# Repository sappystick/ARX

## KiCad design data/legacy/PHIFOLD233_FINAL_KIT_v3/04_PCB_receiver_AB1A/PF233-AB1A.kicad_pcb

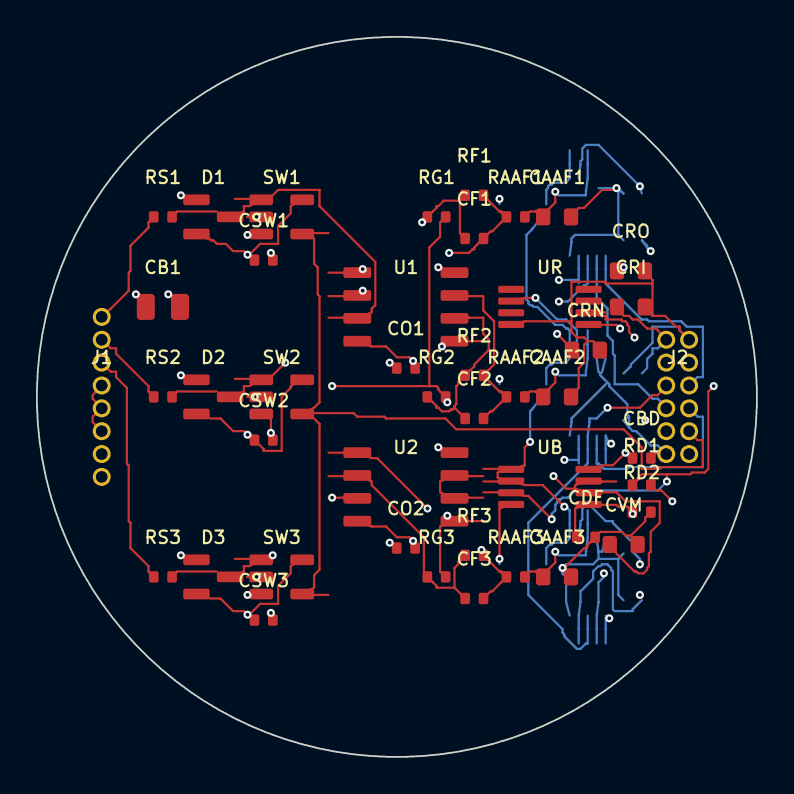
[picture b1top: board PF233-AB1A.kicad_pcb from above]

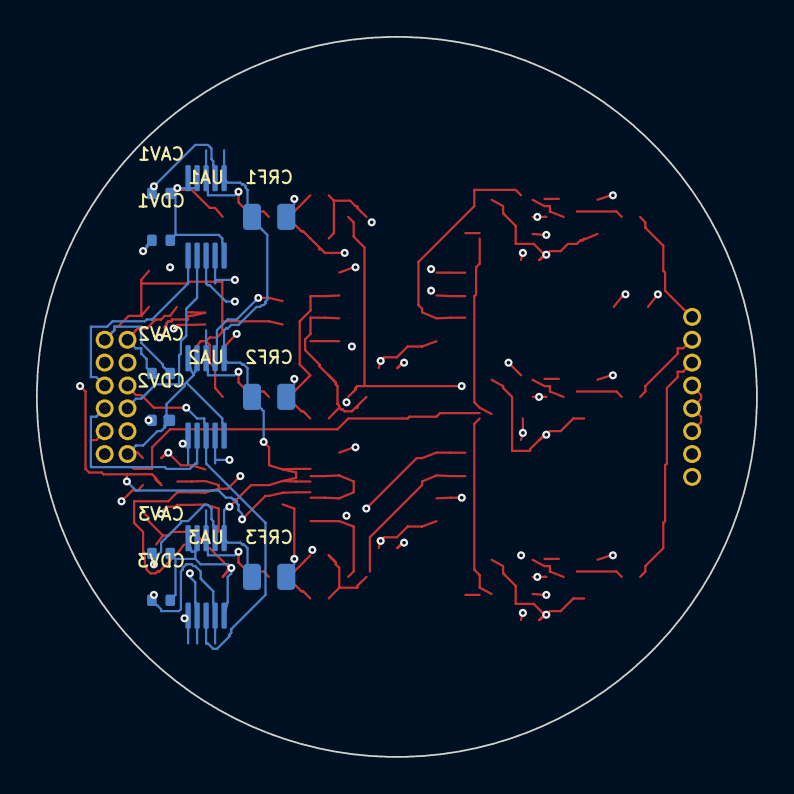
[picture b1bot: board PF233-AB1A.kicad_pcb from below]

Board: 6 copper layers, 40.0 x 40.0 mm, 56 parts (12 on the bottom side), 30 nets.

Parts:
CAAF1, CAAF2, CAAF3: 2n2; C_0603_1608Metric
CAV1, CAV2, CAV3: 100n; C_0402_1005Metric
CB1: 10u; C_0805_2012Metric
CBD: 100n; C_0402_1005Metric
CDF: 100n; C_0402_1005Metric
CDV1, CDV2, CDV3: 100n; C_0402_1005Metric
CF1, CF2, CF3: 22p; C_0402_1005Metric
CO1, CO2: 100n; C_0402_1005Metric
CRF1, CRF2, CRF3: 10u; C_0805_2012Metric
CRI: 1u; C_0603_1608Metric
CRN: 1u; C_0603_1608Metric
CRO: 1u; C_0603_1608Metric
CSW1, CSW2, CSW3: 100n; C_0402_1005Metric
CVM: 1u; C_0603_1608Metric
D1, D2, D3: BAV199; SOT-23
J1: Antenna harness 8p solder pads 1.27mm; PinHeader_1x8_P1.27mm
J2: Main-board 2x6 1.27mm header; PinHeader_2x6_P1.27mm
RAAF1, RAAF2, RAAF3: 200; R_0402_1005Metric
RD1, RD2: 10k; R_0402_1005Metric
RF1, RF2, RF3: 390; R_0402_1005Metric
RG1, RG2, RG3: 10; R_0402_1005Metric
RS1, RS2: 100; R_0402_1005Metric
RS3: 1000; R_0402_1005Metric
SW1, SW2, SW3: 74LVC1G66; SOT-23-5
U1, U2: OPA2211; SOIC-8_3.9x4.9mm_P1.27mm
UA1, UA2, UA3: ADS8860; MSOP-10_3x3mm_P0.5mm
UB: OPA2365; MSOP-8_3x3mm_P0.65mm
UR: REF5041; MSOP-8_3x3mm_P0.65mm

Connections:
+3V3D: CDV1.1, CDV2.1, CDV3.1, J2.3, UA1.9, UA2.9, UA3.9
+5VA: CAV1.1, CAV2.1, CAV3.1, CB1.1, CBD.1, CO1.1, CO2.1, CRI.1, CSW1.1, CSW2.1, CSW3.1, D1.2, D2.2, D3.2, J2.1, SW1.5, SW2.5, SW3.5, U1.8, U2.8, UA1.2, UA2.2, UA3.2, UB.8, UR.2
ADCIN_GX: CAAF1.1, RAAF1.2, UA1.3
ADCIN_GY: CAAF2.1, RAAF2.2, UA2.3
ADCIN_X8: CAAF3.1, RAAF3.2, UA3.3
BLANK: J2.10, SW1.4, SW2.4, SW3.4
CS: J2.6, UA1.6, UA2.6, UA3.6
FB_GX: CF1.1, RF1.1, RG1.1, U1.2
FB_GY: CF2.1, RF2.1, RG2.1, U1.6
FB_X8: CF3.1, RF3.1, RG3.1, U2.2
GND: CAAF1.2, CAAF2.2, CAAF3.2, CAV1.2, CAV2.2, CAV3.2, CB1.2, CBD.2, CDF.2, CDV1.2, CDV2.2, CDV3.2, CO1.2, CO2.2, CRF1.2, CRF2.2, CRF3.2, CRI.2, CRN.2, CRO.2, CSW1.2, CSW2.2, CSW3.2, CVM.2, D1.1, D2.1, D3.1, J1.7, J1.8, J2.2, J2.4, J2.11, J2.12, RD2.2, SW1.3, SW2.3, SW3.3, U1.4, U2.4, UA1.4, UA1.5, UA1.10, UA2.4, UA2.5, UA2.10, UA3.4, UA3.5, UA3.10, UB.4, UR.4
IN_GX: D1.3, RS1.2, SW1.1, U1.3
IN_GY: D2.3, RS2.2, SW2.1, U1.5
IN_X8: D3.3, RS3.2, SW3.1, U2.3
NR: CRN.1, UR.5
OUT_GX: CF1.2, RAAF1.1, RF1.2, U1.1
OUT_GY: CF2.2, RAAF2.1, RF2.2, U1.7
OUT_X8: CF3.2, RAAF3.1, RF3.2, U2.1
RAW_GX: J1.1, RS1.1
RAW_GY: J1.2, RS2.1
RAW_X8: J1.3, RS3.1
SCLK: J2.5, UA1.8, UA2.8, UA3.8
SDO1: J2.7, UA1.7
SDO2: J2.8, UA2.7
SDO3: J2.9, UA3.7
SPARE_OUT_U2: U2.6, U2.7
VCM: CVM.1, J1.4, J1.5, J1.6, RG1.2, RG2.2, RG3.2, SW1.2, SW2.2, SW3.2, U2.5, UB.6, UB.7
VCM_DIV: CDF.1, RD1.2, RD2.1, UB.5
VREF: CRF1.1, CRF2.1, CRF3.1, UA1.1, UA2.1, UA3.1, UB.1, UB.2
VREF_RAW: CRO.1, RD1.1, UB.3, UR.6

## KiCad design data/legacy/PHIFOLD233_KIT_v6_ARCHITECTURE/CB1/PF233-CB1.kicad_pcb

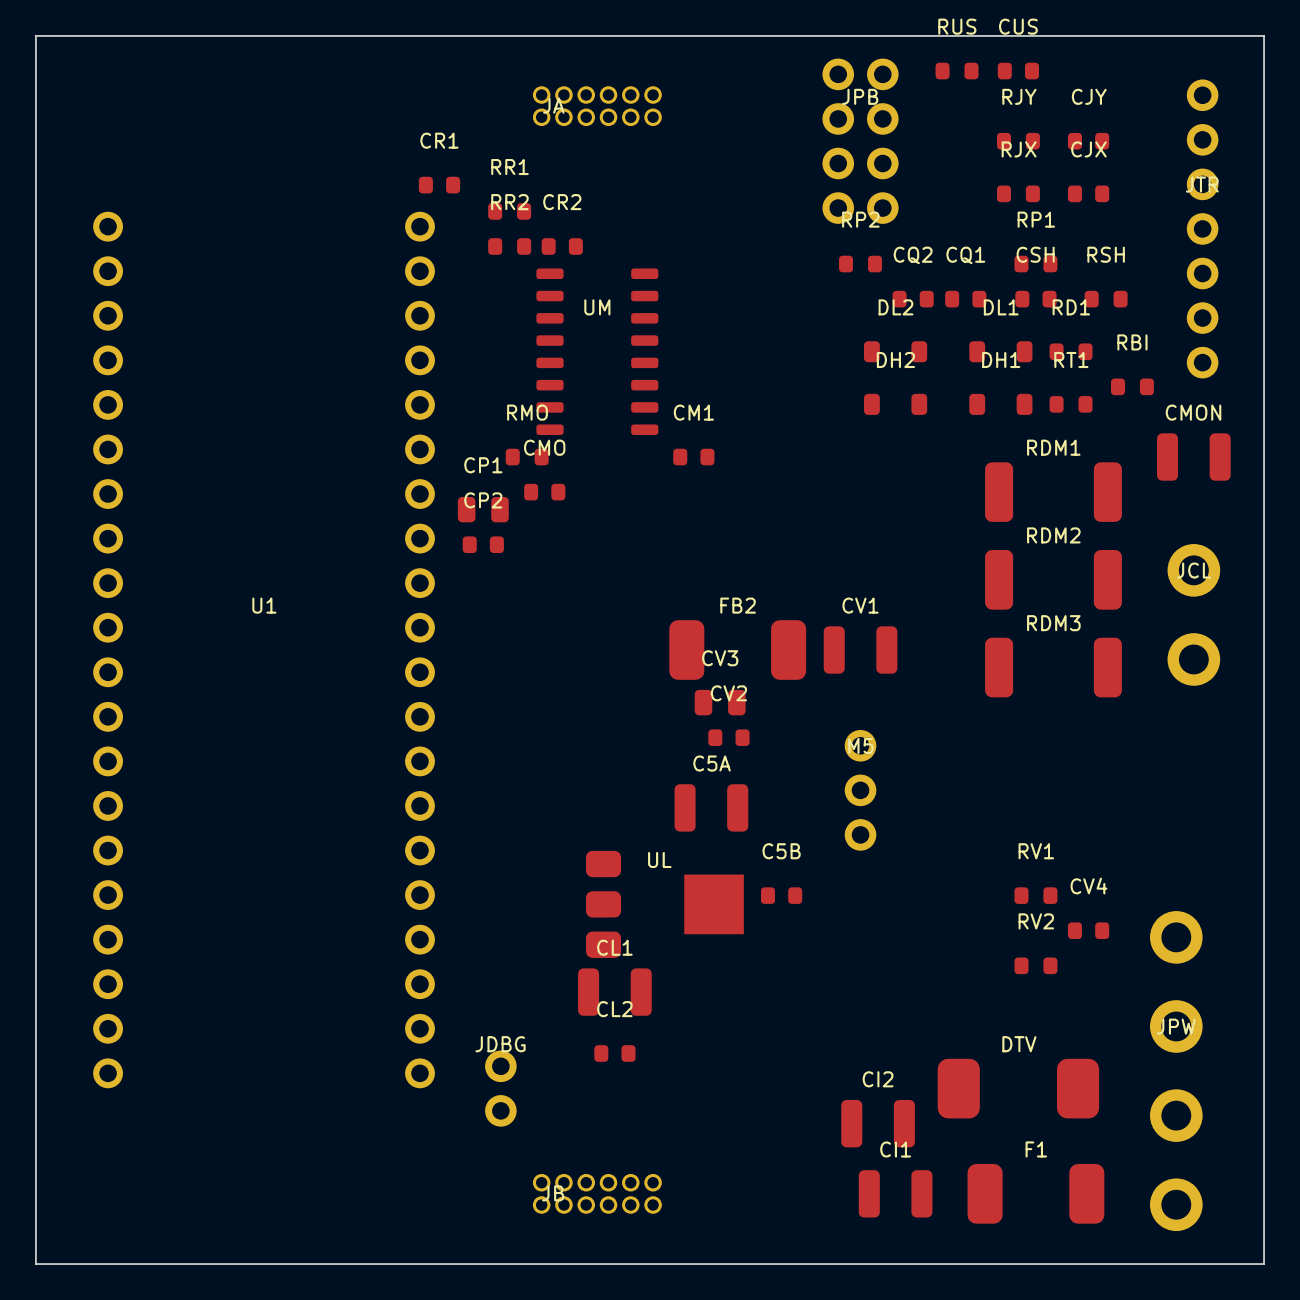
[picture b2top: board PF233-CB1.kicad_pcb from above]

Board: 4 copper layers, 70.0 x 70.0 mm, 58 parts (0 on the bottom side), 44 nets, no tracks yet.

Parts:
C5A: 22u 16V; C_1210_3225Metric
C5B: 100n; C_0603_1608Metric
CI1, CI2: 10u 50V; C_1210_3225Metric
CJX: 10n; C_0603_1608Metric
CJY: 10n; C_0603_1608Metric
CL1: 22u 10V; C_1210_3225Metric
CL2: 100n; C_0603_1608Metric
CM1: 100n; C_0603_1608Metric
CMO: 1n; C_0603_1608Metric
CMON: 100n 630V; C_1210_3225Metric
CP1: 10u 10V; C_0805_2012Metric
CP2: 100n; C_0603_1608Metric
CQ1, CQ2: 10n; C_0603_1608Metric
CR1, CR2: 1u; C_0603_1608Metric
CSH: 1n 100V; C_0603_1608Metric
CUS: 1n 100V; C_0603_1608Metric
CV1: 10u 16V; C_1210_3225Metric
CV2, CV4: 100n; C_0603_1608Metric
CV3: 1u; C_0805_2012Metric
DH1, DH2: BAS16; D_SOD-123
DL1, DL2: BAS16; D_SOD-123
DTV: SMCJ33A; D_SMC
F1: 5A slow 32V; Fuse_1812_4532Metric
FB2: ferrite bead 1 A; L_1812_4532Metric
JA: to AB1A J2; Pin_header_1.27_2x6_P1.27mm
JB: to AB1B J2; Pin_header_1.27_2x6_P1.27mm
JCL: Coil leads from the neck module: COIL_B (drain si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; Terminal_block_1x2_P5.08mm
JDBG: RUN / GND (reset, SWD pads on Pico underside); Pin_header_1x2_P2.54mm
JPB: to PB1R: 12V GND TX1_IN REF_I1 FAULT1_N ISENSE1 N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; Pin_header_2x4_P2.54mm
JPW: Power in: VBUS VBUS GND GND (from shaft); Terminal_block_1x4_P5.08mm
JTR: Handle: +3V3 GND TRIG DIAL JOYX JOYY SHLD; Pin_header_1x7_P2.54mm
M5: 5 V 1.5 A switching module; Converter_DCDC_Murata_OKI-78SR_Horizontal
RBI: 100k; R_0603_1608Metric
RD1: 1k; R_0603_1608Metric
RDM1, RDM2, RDM3: 110R; R_2512_6332Metric
RJX: 1k; R_0603_1608Metric
RJY: 1k; R_0603_1608Metric
RMO: 1k; R_0603_1608Metric
RP1, RP2: 10k; R_0603_1608Metric
RR1, RR2: 10k; R_0603_1608Metric
RSH: 1M; R_0603_1608Metric
RT1: 1k; R_0603_1608Metric
RUS: 1M; R_0603_1608Metric
RV1: 100k; R_0603_1608Metric
RV2: 10k; R_0603_1608Metric
U1: Pico 2 W; RaspberryPi_Pico_Common_THT
UL: AMS1117-3.3; SOT-223-3_TabPin2
UM: 74HC4051; SOIC-16_3.9x9.9mm_P1.27mm

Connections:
+3V3D: CL1.1, CL2.1, JA.3, JB.3, UL.2, UL.4
+5V: C5A.1, C5B.1, CP1.1, CP2.1, FB2.1, M5.3, U1.39, UL.3
+5VA: CV1.1, CV2.1, CV3.1, FB2.2, JA.1, JB.1
BLANK: JA.10, JB.9, U1.4
COIL_A: JCL.2, RDM3.2
COIL_B: CMON.1, JCL.1, RDM1.1
CS: JA.6, JB.6, U1.6
DIAL_EXT: JTR.4, RD1.1
DIAL_IN: CQ2.1, DH2.2, DL2.1, RD1.2, RP2.1, U1.32
DM1: RDM1.2, RDM2.1
DM2: RDM2.2, RDM3.1
FAULT1_N: JPB.5, U1.15
GND: C5A.2, C5B.2, CI1.2, CI2.2, CJX.2, CJY.2, CL1.2, CL2.2, CM1.2, CMO.2, CP1.2, CP2.2, CQ1.2, CQ2.2, CR1.2, CR2.2, CSH.2, CUS.2, CV1.2, CV2.2, CV3.2, CV4.2, DL1.2, DL2.2, DTV.2, JA.2, JA.4, JA.11, JA.12, JB.2, JB.4, JB.12, JDBG.2, JPB.2, JPB.8, JPW.3, JPW.4, JTR.2, M5.2, RSH.2, RUS.2, RV2.2, U1.3, U1.8, U1.13, U1.18, U1.23, U1.28, U1.33, U1.38, UL.1, UM.1, UM.2, UM.4, UM.5, UM.6, UM.7, UM.8, UM.9
ISENSE1: JPB.6, UM.13
JOY_X: JTR.5, RJX.1
JOY_XF: CJX.1, RJX.2, UM.15
JOY_Y: JTR.6, RJY.1
JOY_YF: CJY.1, RJY.2, UM.12
MONO_IN: CMON.2, JB.10, RBI.1
MUX_COM: RMO.1, UM.3
MUX_OUT: CMO.1, RMO.2, U1.31
MUX_S0: U1.24, UM.11
MUX_S1: U1.25, UM.10
NTC_SENSE: JPB.7, UM.14
P3V3: CM1.1, DH1.1, DH2.1, JTR.1, RP1.2, RP2.2, U1.36, UM.16
REF_I1: CR2.1, JPB.4, RR2.2
REF_N1: CR1.1, RR1.2, RR2.1
REF_PWM1: RR1.1, U1.17
RUN: JDBG.1, U1.30
SCLK: JA.5, JB.5, U1.5
SDOA1: JA.7, U1.9
SDOA2: JA.8, U1.10
SDOA3: JA.9, U1.11
SDOB1: JB.7, U1.12
SDOB2: JB.8, U1.14
SHIELD: CSH.1, JTR.7, RSH.1
TRIG_EXT: JTR.3, RT1.1
TRIG_IN: CQ1.1, DH1.2, DL1.1, RP1.1, RT1.2, U1.7
TX1_IN: JPB.3, U1.1
UMB_SHLD: CUS.1, JPB.1, RUS.1
VBUS: CI1.1, CI2.1, DTV.1, F1.2, M5.1, RV1.1
VBUS_IN: F1.1, JPW.1, JPW.2
VBUS_SENSE: CV4.1, RV1.2, RV2.1, U1.34
VCM_OUT: JB.11, RBI.2

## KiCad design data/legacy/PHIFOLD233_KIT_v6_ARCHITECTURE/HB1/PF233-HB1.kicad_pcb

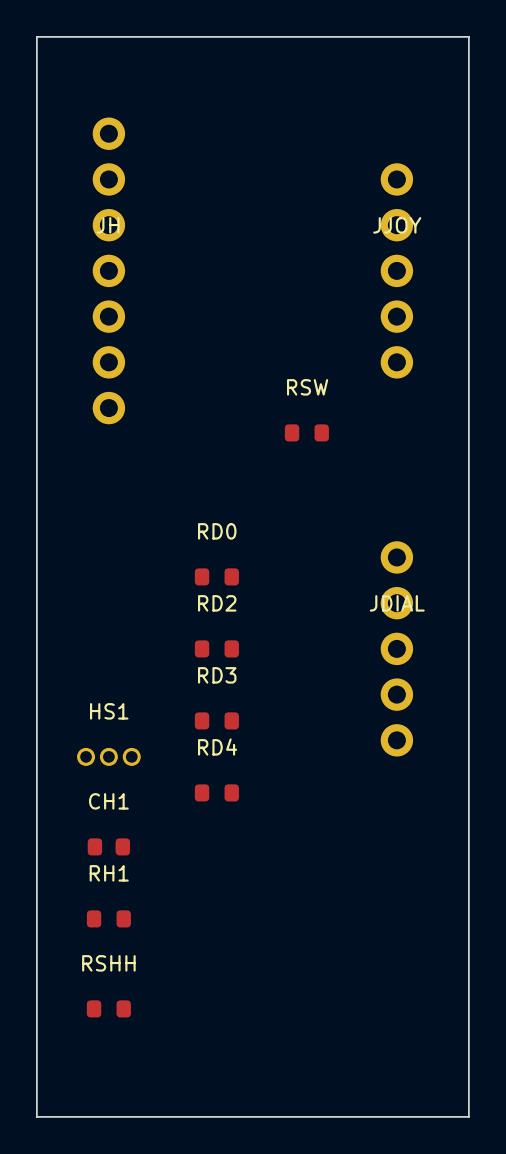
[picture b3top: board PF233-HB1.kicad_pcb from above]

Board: 4 copper layers, 24.0 x 60.0 mm, 12 parts (0 on the bottom side), 12 nets, no tracks yet.

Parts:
CH1: 100n; C_0603_1608Metric
HS1: SS49E; TO-92_Inline
JDIAL: Dial: COM P1 P2 P3 P4 (4-position rotary switch); Pin_header_1x5_P2.54mm
JH: Cable to head: +3V3 GND TRIG DIAL JOYX JOYY SHLD; Pin_header_1x7_P2.54mm
JJOY: Joystick: V GND X Y SW; Pin_header_1x5_P2.54mm
RD0, RD3: 10k; R_0603_1608Metric
RD2: 3k3; R_0603_1608Metric
RD4: 33k; R_0603_1608Metric
RH1: 1k; R_0603_1608Metric
RSHH: 0R; R_0603_1608Metric
RSW: 10k; R_0603_1608Metric

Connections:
DIAL: JDIAL.1, JH.4, RD0.2
DP2: JDIAL.3, RD2.1
DP3: JDIAL.4, RD3.1
DP4: JDIAL.5, RD4.1
GND: CH1.2, HS1.2, JDIAL.2, JH.2, JJOY.2, RD2.2, RD3.2, RD4.2, RSHH.2
HALL_OUT: HS1.3, RH1.1
JOY_SW: JJOY.5, RSW.1
JOY_X: JH.5, JJOY.3
JOY_Y: JH.6, JJOY.4
P3V3: CH1.1, HS1.1, JH.1, JJOY.1, RD0.1, RSW.2
SHIELD: JH.7, RSHH.1
TRIG: JH.3, RH1.2

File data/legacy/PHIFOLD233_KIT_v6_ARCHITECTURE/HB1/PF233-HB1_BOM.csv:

Qty,Refs,Type,Value,MPN / note,Footprint
1,CH1,C0603,100n,,Capacitor_SMD:C_0603_1608Metric
1,JDIAL,HDR1x5,Dial: COM P1 P2 P3 P4 (4-position rotary switch),4-position rotary switch,Connector:Pin_header_1x5_P2.54mm
1,JJOY,HDR1x5,Joystick: V GND X Y SW,2-axis thumb joystick module,Connector:Pin_header_1x5_P2.54mm
1,JH,HDR1x7,Cable to head: +3V3 GND TRIG DIAL JOYX JOYY SHLD,shielded 6-core + drain,Connector:Pin_header_1x7_P2.54mm
1,RSHH,R0603,0R,shield to grip foil,Resistor_SMD:R_0603_1608Metric
2,"RD0,RD3",R0603,10k,,Resistor_SMD:R_0603_1608Metric
1,RSW,R0603,10k,joystick switch pull-up,Resistor_SMD:R_0603_1608Metric
1,RH1,R0603,1k,,Resistor_SMD:R_0603_1608Metric
1,RD4,R0603,33k,,Resistor_SMD:R_0603_1608Metric
1,RD2,R0603,3k3,,Resistor_SMD:R_0603_1608Metric
1,HS1,SS49E,SS49E,Honeywell SS49E linear Hall (trigger magnet travel 0-4 mm),Package_TO_SOT_THT:TO-92_Inline

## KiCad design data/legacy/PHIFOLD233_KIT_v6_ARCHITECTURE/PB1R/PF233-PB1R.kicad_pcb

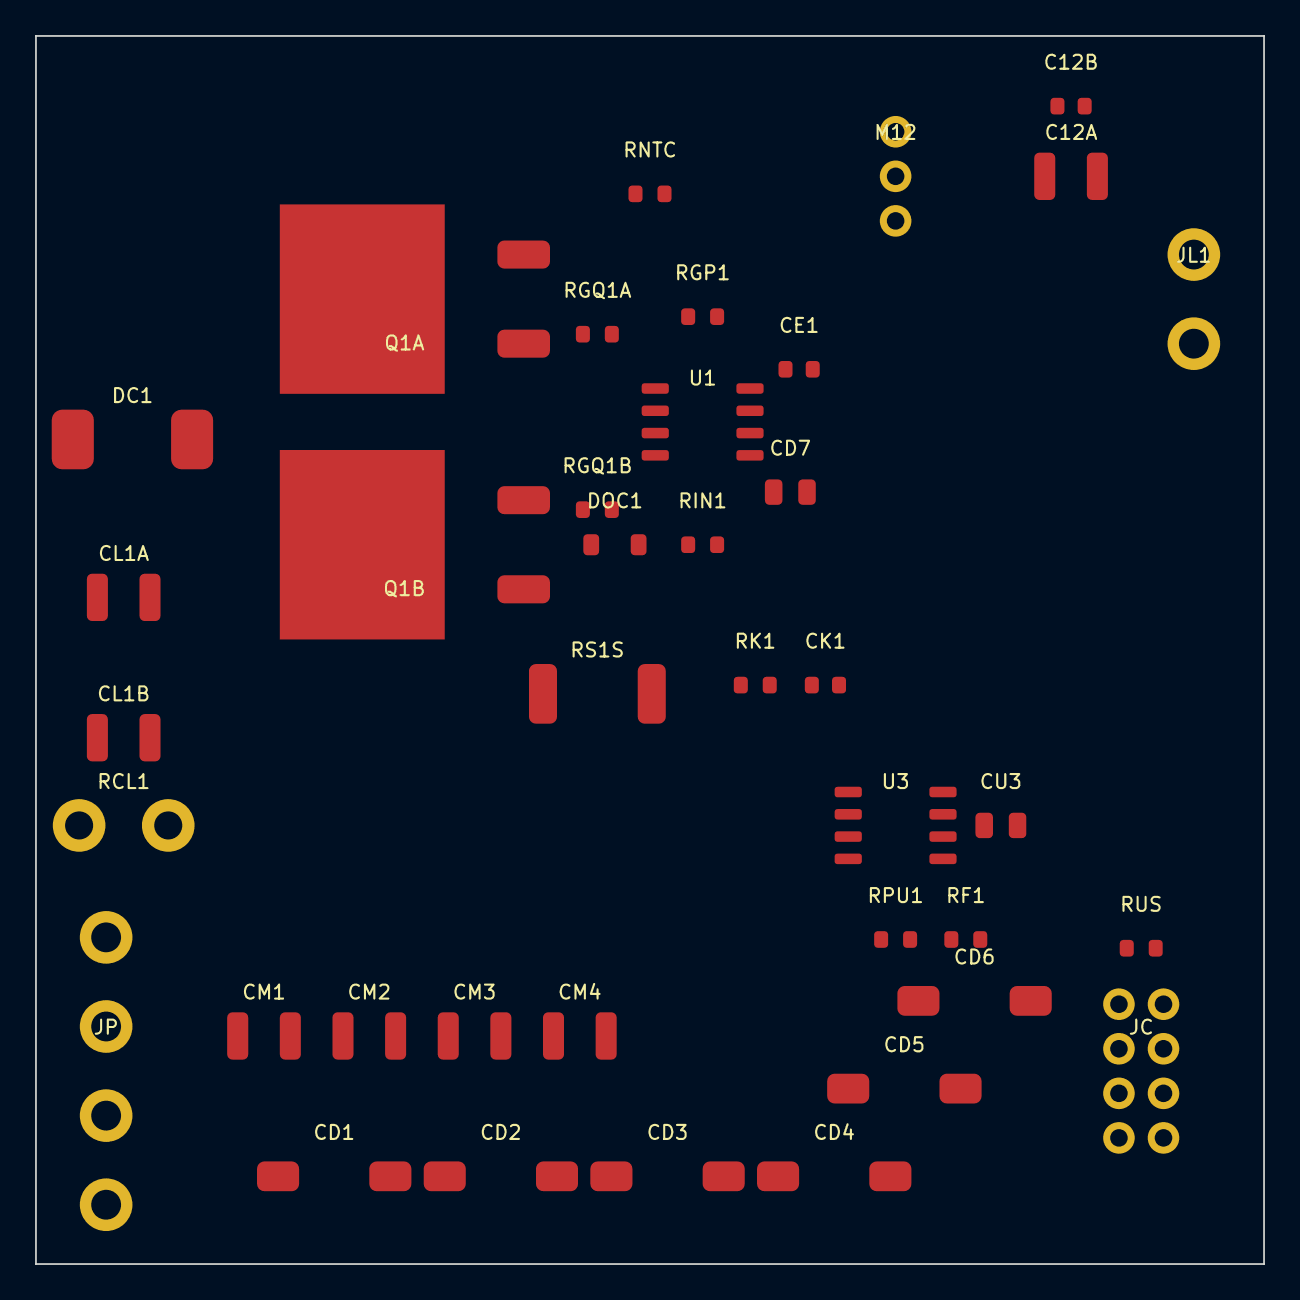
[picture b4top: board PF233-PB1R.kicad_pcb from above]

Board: 4 copper layers, 70.0 x 70.0 mm, 39 parts (0 on the bottom side), 17 nets, no tracks yet.

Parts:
C12A: 22u 25V; C_1210_3225Metric
C12B: 100n; C_0603_1608Metric
CD1, CD2, CD3, CD4, CD5, CD6: 150u 35V polymer Ta; CP_EIA-7343-43_Kemet-X
CD7: 1u 25V; C_0805_2012Metric
CE1: 100n; C_0603_1608Metric
CK1: 100p; C_0603_1608Metric
CL1A, CL1B: 100n 630V; C_1210_3225Metric
CM1, CM2, CM3, CM4: 10u 50V; C_1210_3225Metric
CU3: 1u 25V; C_0805_2012Metric
DC1: ES3J 600V 3A; D_SMC
DOC1: BAS16; D_SOD-123
JC: Umbilical from the head: SHLD GND TX1_IN REF_I1 F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; Pin_header_2x4_P2.54mm
JL1: Coil outer band: DRAIN, VBUS; Terminal_block_1x2_P5.08mm
JP: Power in: VBUS VBUS GND GND; Terminal_block_1x4_P5.08mm
M12: 12 V 1.5 A switching module; Converter_DCDC_Murata_OKI-78SR_Horizontal
Q1A, Q1B: 650V SJ 95mR; TO-263-3_TabPin2
RCL1: external 5k 10W (lid bank); SolderPad_2x_P5.08mm
RF1: 1k; R_0603_1608Metric
RGP1: 10k; R_0603_1608Metric
RGQ1A, RGQ1B: 10; R_0603_1608Metric
RIN1: 100; R_0603_1608Metric
RK1: 100; R_0603_1608Metric
RNTC: 10k NTC; R_0603_1608Metric
RPU1: 10k; R_0603_1608Metric
RS1S: 10m 3W; R_2512_6332Metric
RUS: 1M; R_0603_1608Metric
U1: TC4420; SOIC-8_3.9x4.9mm_P1.27mm
U3: LM393; SOIC-8_3.9x4.9mm_P1.27mm

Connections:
AUX12: C12A.1, C12B.1, CD7.1, CE1.1, CU3.1, M12.3, RPU1.2, U1.1, U1.8, U3.8
CLAMP1: CL1A.1, CL1B.1, DC1.1, RCL1.1
DRAIN1: DC1.2, JL1.1, Q1A.2, Q1B.2
DRVIN1: DOC1.2, RIN1.2, U1.2
FAULT1_N: JC.5, RF1.2
G1: RGP1.1, RGQ1A.1, RGQ1B.1, U1.6, U1.7
GATE_Q1A: Q1A.1, RGQ1A.2
GATE_Q1B: Q1B.1, RGQ1B.2
GND: C12A.2, C12B.2, CD1.2, CD2.2, CD3.2, CD4.2, CD5.2, CD6.2, CD7.2, CE1.2, CK1.2, CM1.2, CM2.2, CM3.2, CM4.2, CU3.2, JC.2, JC.8, JP.3, JP.4, M12.2, RGP1.2, RNTC.2, RS1S.2, RUS.2, U1.4, U1.5, U3.4, U3.5, U3.6
ISENSE1: CK1.1, JC.6, RK1.2, U3.2
NTC_SENSE: JC.7, RNTC.1
OC1_OUT: DOC1.1, RF1.1, RPU1.1, U3.1
REF_I1: JC.4, U3.3
SRC1: Q1A.3, Q1B.3, RK1.1, RS1S.1
TX1_IN: JC.3, RIN1.1
UMB_SHLD: JC.1, RUS.1
VBUS: CD1.1, CD2.1, CD3.1, CD4.1, CD5.1, CD6.1, CL1A.2, CL1B.2, CM1.1, CM2.1, CM3.1, CM4.1, JL1.2, JP.1, JP.2, M12.1, RCL1.2

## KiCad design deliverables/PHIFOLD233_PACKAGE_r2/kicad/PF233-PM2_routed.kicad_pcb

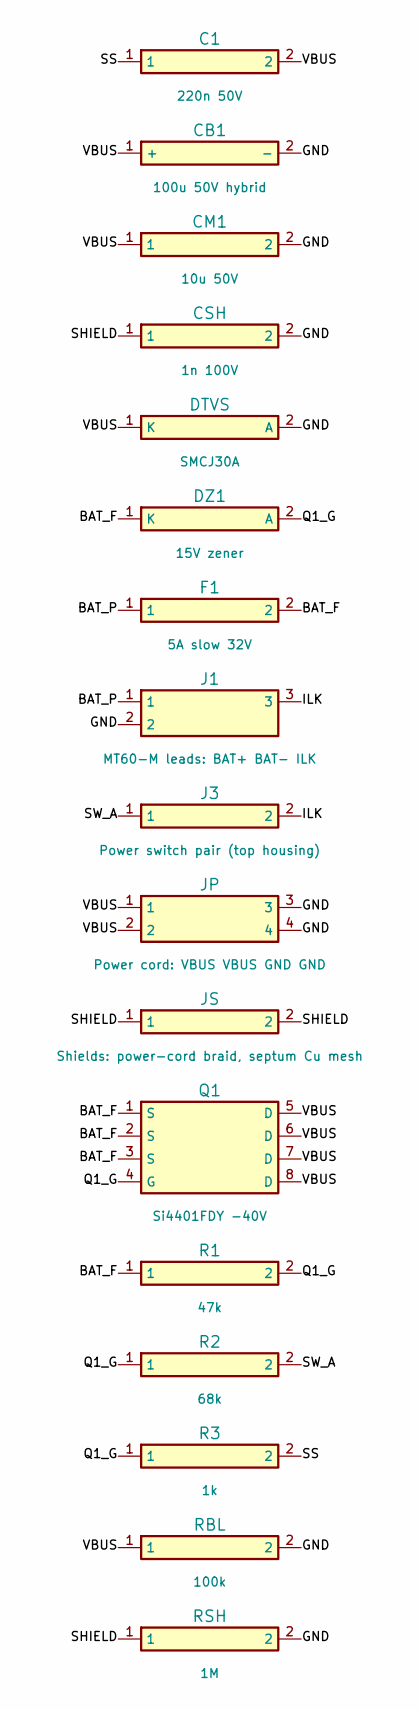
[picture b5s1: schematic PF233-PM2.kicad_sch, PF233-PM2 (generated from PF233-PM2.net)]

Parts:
C1: 220n 50V; C_0805_2012Metric
CB1: 100u 50V hybrid; CP_Elec_10x10
CM1: 10u 50V; C_1210_3225Metric
CSH: 1n 100V; C_0603_1608Metric
DTVS: SMCJ30A; D_SMC
DZ1: 15V zener; D_SOD-123
F1: 5A slow 32V; Fuse_1206_3216Metric
J1: MT60-M leads: BAT+ BAT- ILK; Wire_pads_1x3_P5.08mm
J3: Power switch pair (top housing); Wire_pads_1x2_P2.54mm
JP: Power cord: VBUS VBUS GND GND; Wire_pads_1x4_P5.08mm
JS: Shields: power-cord braid, septum Cu mesh; Wire_pads_1x2_P2.54mm
Q1: Si4401FDY -40V; SOIC-8_3.9x4.9mm_P1.27mm
R1: 47k; R_0603_1608Metric
R2: 68k; R_0603_1608Metric
R3: 1k; R_0603_1608Metric
RBL: 100k; R_1206_3216Metric
RSH: 1M; R_0603_1608Metric

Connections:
BAT_F: DZ1.1 (K), F1.2, Q1.1 (S), Q1.2 (S), Q1.3 (S), R1.1
BAT_P: F1.1, J1.1
GND: CB1.2 (-), CM1.2, CSH.2, DTVS.2 (A), J1.2, JP.3, JP.4, RBL.2, RSH.2
ILK: J1.3, J3.2
Q1_G: DZ1.2 (A), Q1.4 (G), R1.2, R2.1, R3.1
SHIELD: CSH.1, JS.1, JS.2, RSH.1
SS: C1.1, R3.2
SW_A: J3.1, R2.2
VBUS: C1.2, CB1.1 (+), CM1.1, DTVS.1 (K), JP.1, JP.2, Q1.5 (D), Q1.6 (D), Q1.7 (D), Q1.8 (D), RBL.1

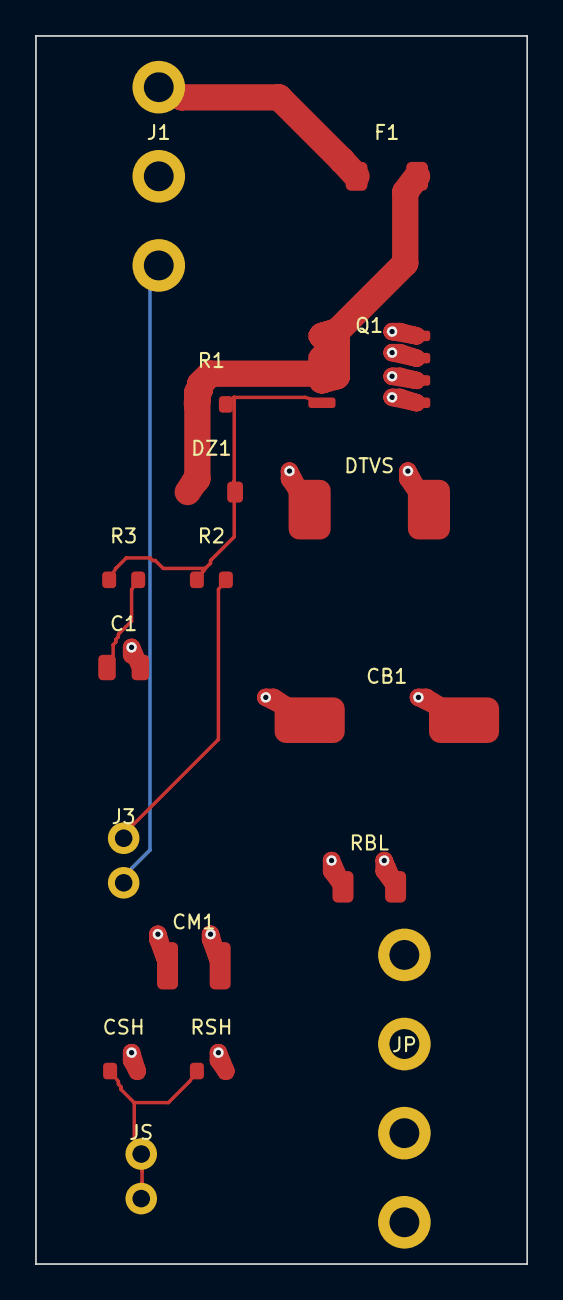
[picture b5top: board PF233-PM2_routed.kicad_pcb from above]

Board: 4 copper layers, 28.0 x 70.0 mm, 17 parts (0 on the bottom side), 9 nets.
